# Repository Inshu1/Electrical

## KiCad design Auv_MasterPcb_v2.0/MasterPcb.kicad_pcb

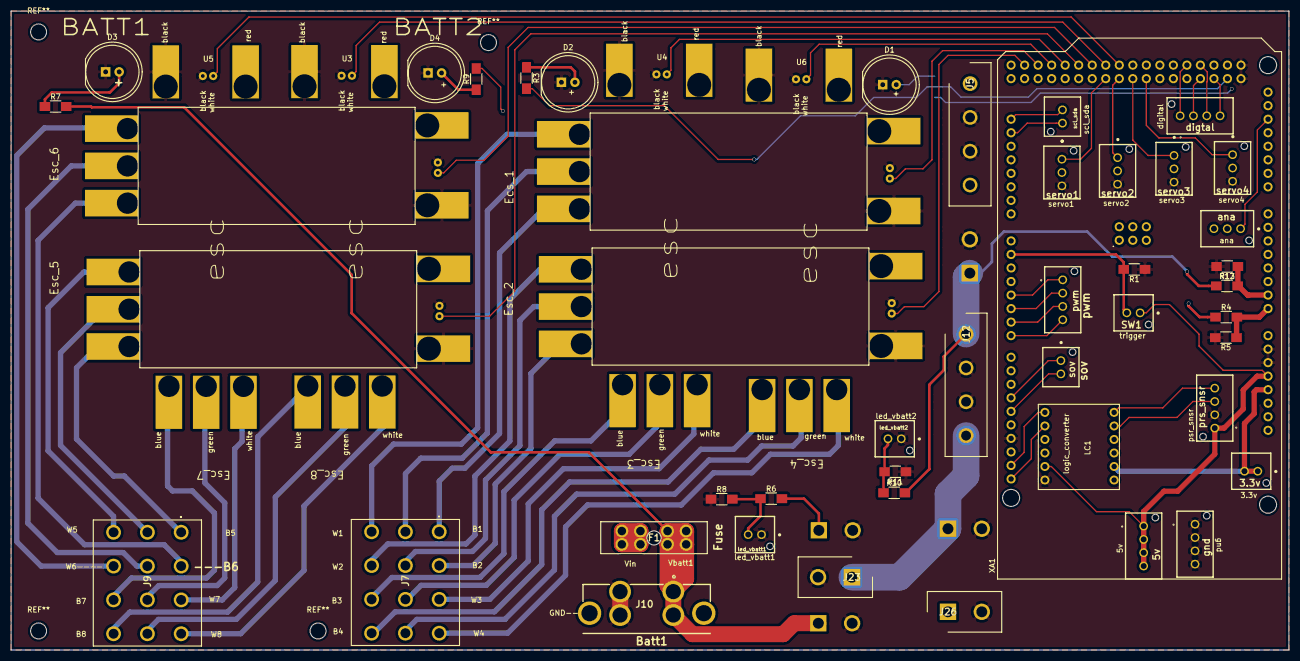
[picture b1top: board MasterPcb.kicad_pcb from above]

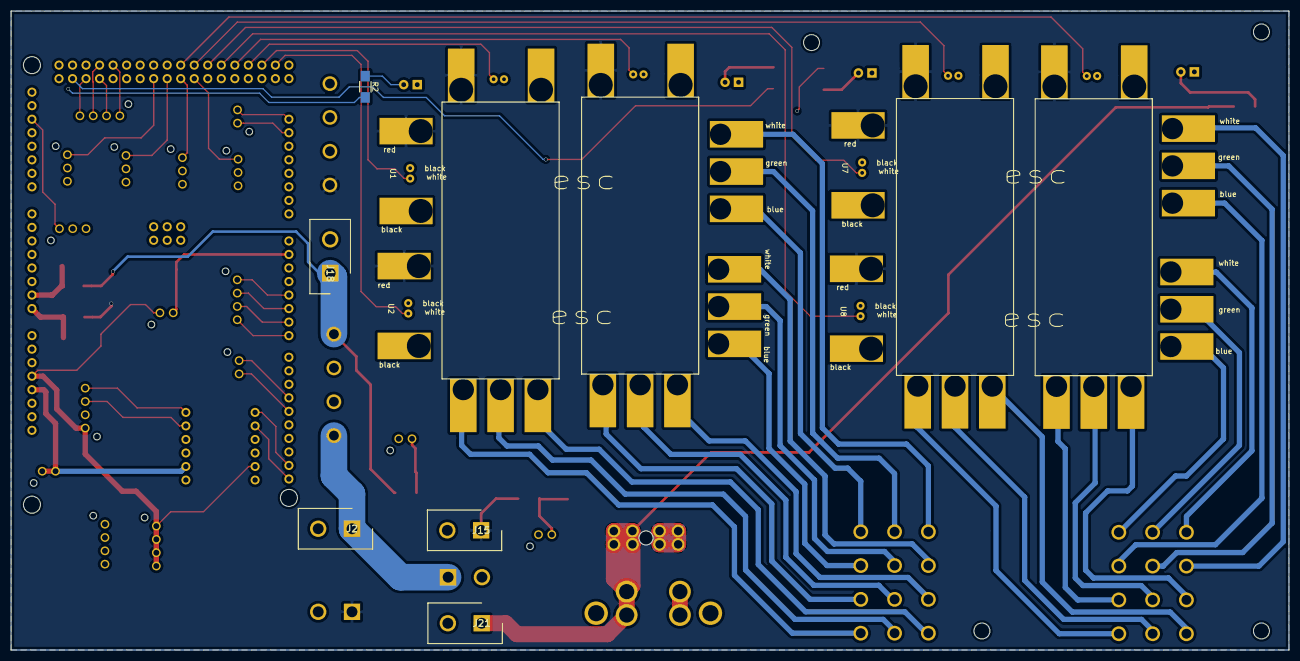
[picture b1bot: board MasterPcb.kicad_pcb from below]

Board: 4 copper layers, 240.0 x 120.0 mm, 55 parts (9 on the bottom side), 74 nets.

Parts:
3.3v: 3.3V_extras; 1x2_mini_lock
5v: 5V_extra; 1x4_mini_lock
D1, D2, D3, D4: LED; LED_D10.0mm
F1: Fuse
J2: nuc_battery; 1x2_Molex
J5: 5V_buck_servo; 1x4_Molex
J7: Thruster_1-4; 4_3connector
J9: Thruster_5-8; 4_3connector
J10: Thruster_power; power
J12: 19V_buck_nuc; 1x4_Molex
J15: dvl_power; 1x2_Molex
J18: Nuc_power; 1x2_Molex
J21: vbatt1_powerout; 1x2_Molex
J23: vbatt2_powerout; 1x2_Molex
J26: Sov_powerout; 1x2_Molex
LC1: Logic_Converter
R1, R2, R3, R5, R7, R9, R13: 1K; R_1206_HandSoldering
R4, R12: 24K; R_1206_HandSoldering
R6, R10: 1k; R_1206_HandSoldering
R8, R11: 4k; R_1206_HandSoldering
SW1: SW_DIP_x01; 1x2_mini_lock
U1, U2, U7, U8: ESCPINS; esc_redefined
U3, U4, U5, U6: ESCPINS; esc_mirror_redefined
XA1: Arduino_Mega2560_Shield
ana: Analog_Extras; 1x3_mini_lock
digtal: Dig_Extras; 1x4_mini_lock
gnd: GND_extras; 1x4_mini_lock
led_vbatt1: Led_vbatt1; 1x2_mini_lock
led_vbatt2: Led_vbatt2; 1x2_mini_lock
prs_snsr: Pressure_sensor_conn; 1x4_mini_lock
pwm: PWM_extras; 1x4_mini_lock
scl_sda: SDA_SCL_extras; 1x2_mini_lock
servo1: servo1; 1x3_mini_lock
servo2: servo2; 1x3_mini_lock
servo3: servo3; 1x3_mini_lock
servo4: servo4; 1x3_mini_lock
sov: Sov; 1x2_mini_lock

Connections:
/3.3V: 3.3v.1, 3.3v.2, LC1.8, XA1.3V3
/5V: 5v.1, 5v.2, 5v.3, 5v.4, LC1.2, SW1.1, XA1.5V1, prs_snsr.1
/5VBC: J5.1, servo1.2, servo2.2, servo3.2, servo4.2
/A0: R4.2, R5.1, XA1.A0
/A1: R12.2, R13.1, XA1.A1
/ANA1: XA1.A13, ana.1
/ANA2: XA1.A14, ana.2
/ANA3: XA1.A15, ana.3
/B1: J7.1, U1.1
/B2: J7.4, U2.1
/B3: J7.9, U4.3
/B4: J7.12, U6.3
/B5: J9.1, U8.1
/B6: J9.4, U7.1
/B7: J9.9, U5.3
/B8: J9.12, U3.3
/DIG1: XA1.D47, digtal.1
/DIG2: XA1.D48, digtal.2
/DIG3: XA1.D49, digtal.3
/DIG4: XA1.D50, digtal.4
/DVL: F1.5, F1.6, F1.7, F1.8, J5.4, J15.1, J26.1, R4.1, R6.2, U1.6, U2.6, U3.7, U4.7, U5.7, U6.7, U7.6, U8.6
/G1: J7.2, U1.2
/G2: J7.5, U2.2
/G3: J7.8, U4.2
/G4: J7.11, U6.2
/G5: J9.2, U8.2
/G6: J9.5, U7.2
/G7: J9.8, U5.2
/G8: J9.11, U3.2
/IN_1: XA1.D11, sov.1
/IN_2: XA1.D12, sov.2
/Led_vbatt1: R6.1, R8.2, led_vbatt1.2
/Led_vbatt2: R10.1, R11.2, led_vbatt2.2
/NUC: J12.1, J18.1, R10.2, R12.1
/PWM-1: XA1.D4, pwm.1
/PWM-2: XA1.D5, pwm.2
/PWM-3: XA1.D6, pwm.3
/PWM-4: XA1.D7, pwm.4
/SCL1: XA1.D21, scl_sda.2
/SCL(HV): LC1.5, XA1.SCL
/SCL(PS): LC1.11, prs_snsr.3
/SDA1: XA1.D20, scl_sda.1
/SDA(HV): LC1.6, XA1.SDA
/SDA(PS): LC1.12, prs_snsr.4
/SER1: XA1.D34, servo1.1
/SER2: XA1.D36, servo2.1
/SER3: XA1.D38, servo3.1
/SER4: XA1.D40, servo4.1
/T-1: U1.4, XA1.D25
/T-2: U2.4, XA1.D23
/T-3: U4.4, XA1.D29
/T-4: U6.4, XA1.D27
/T-5: U8.4, XA1.D31
/T-6: U7.4, XA1.D33
/T-7: U5.4, XA1.D37
/T-8: U3.4, XA1.D35
/Test_led1: R3.2, XA1.D52
/Test_led2: R2.2, XA1.D53
/Trigger: R1.2, SW1.2, XA1.D1
/VBATT1: F1.1, F1.2, F1.3, F1.4, J10.1, J10.2, J21.1, R7.2
/VBATT2: J2.1, J12.4, J23.1, R9.2
/W1: J7.3, U1.3
/W2: J7.6, U2.3
/W3: J7.7, U4.1
/W4: J7.10, U6.1
/W5: J9.3, U8.3
/W6: J9.6, U7.3
/W7: J9.7, U5.1
/W8: J9.10, U3.1
GND: D1.1, D2.1, D3.1, D4.1, J2.2, J5.2, J5.3, J10.3, J10.4, J12.2, J12.3, J15.2, J18.2, J21.2, J23.2, J26.2, LC1.1, R1.1, R5.2, R8.1, R11.1, R13.2, U1.5, U1.7, U2.5, U2.7, U3.5, U3.6, U4.5, U4.6, U5.5, U5.6, U6.5, U6.6, U7.5, U7.7, U8.5, U8.7, XA1.GND1, XA1.GND2, XA1.GND3, XA1.GND5, XA1.GND6, gnd.1, gnd.2, gnd.3, gnd.4, led_vbatt1.1, led_vbatt2.1, prs_snsr.2, servo1.3, servo2.3, servo3.3, servo4.3
unnamed: D1.2, R2.1
unnamed: D2.2, R3.1
unnamed: D3.2, R7.1
unnamed: D4.2, R9.1

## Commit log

2018-12-04 adc code
2018-12-06 analog part pcb
2019-06-14 master pcb
2019-06-26 Master PCB version 2.0
